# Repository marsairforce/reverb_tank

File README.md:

# A stand alone spring reverb tank

Here I wanted to investigate using op-amps to drive the tank, rather than to build a tube circuit.

I already built a tube circuit into my Traynor amp, and I am very happy with how good it sounds.

I just had this spare reverb tank sitting on my shelf with nothing to make use of it. If i can build it into a "pedal" type of effect, I can power it from standard guitar pedal power supply and use it in my audio hobby work. Like as an effect for microphone for vocals. Or drums in reaper. Any time reverb is needed so I don't need to use an effect or impulse response, Since these always sound terrible to me.

But then I had the idea, Why not just build both as a stand-alone unit. Have a switch to change between which driver is used.

## Packaging

The reverb tank is quite long. If I could build a 1U rack case for this that might be fun. But then might as well build a power supply so this plugs in. I can create a stripped down version of the op-amp power supply, having a single fixed +/-15V regulated output. That power supply is super awesome. Smooth DC ouput

The challenge is I need to be able to create a metal chassis. or shell out to buy one.

I found one from Bud Industries for about half what the Hammond mfg one was. But the Hammond one is painted. This 1U chasis needs painting then. It is about $100 to get the chassis and lid.

But the idea is I think I can fit this into a 1U chassis.

## Op-Amp Driver

I am really inspired by the design from [Elliot Sound](https://sound-au.com/project34.htm) site.

I find it curious, that when doing a google search I found several foreign websites that look like a pintrest kind of site but caching super old versions of this page, the wording is mostly the same, but the schematic showed a simple LM386 in place there for the driver to the reverb tank.

This makes me question, why?  Because before doing research into this I was thinking about using a 386 audio amplifier IC here. My theory is that it was not able to produce a good quality drive to the reverb tank. Or that the output was somewhat noisy.  Or was it just some amp design used the 386 and threatened to sue him for copyright?

Spend an evening capturing the schematic. And the power supply (see below)

## Tube Driver

I find myself again back on [The Valve Wizard](http://www.valvewizard.co.uk/reverbdriver.html) site. The discussion there is about how the using the EL84 as a driving tube is overkill and waste. Sure. But it does work.And I simply love the sound of it.

So I think I will basically take the same schematic I ended up using in the Traynor amplifier and making it a stand-alone driver into this chassis.

This is loosely based on the [Tube Town Reverb Kit](https://www.tube-town.net/cms/userfiles/media/low-reverb/kit-tubereverb.pdf)

I guess this project I am basically building that thing.

## Power Supply

The first challenge for either approach is I yet again need to build another power supply. Sometimes it feels like all I do is build a power supply for a project and by the time I figure that out I either get bored with the project and have moved on or run out of budget and give up.

If I do tubes, I need the 350V DC and the 6.3V filament supply.

If I do op-amps I need +/-15V. probably the current from the op-amp power supply project. So I can just reuse the same transformer, capacitors and a different regulator. I have a feeling this is going to be more practical. In that it is going to cost less to build, will operate with less need for cooling (e.g. in an audio rack) and have a better chance of fitting into a 1U rack chassis.

So I think I'll just build the op-amp based driver.

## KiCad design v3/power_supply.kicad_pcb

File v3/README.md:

# A second attempt at using op-amps to drive a spring reverb tank

Following the failure of the first attempt and several months, I came back to attempting this again.

This time using some of the knowledge I have learned along the way.

* To use a pre-built power supply module. These Recom power converters are basically cheaper than anything I can build, more efficient, better quality power output, And a single package can not be more convenient.

* To use the simple op-amp that powers a push pull output transistor like I had before for my desktop audio amp and speakers. I mean, here I am driving a spring. it doesn't need to be really good quality hifi audio. It just needs to make the spring move enought that we can pick up its sound.

* To use the boost converter I designed for my guitars. Here this is a v2 design I did a while ago but never got around to actually building, because I didn't need it.

So I set out the Father's day weekend to build 3 small modules.

They fit into the chassis I had used before. So that is good to recycle it.

This time, testing each component as I go on its own.

First I connected the tank on its own. Using my desk audio amplifier to drive it and just sending it back to my mic preamp to hear how it sounds.  The tank on its own is pretty quiet. Good.

I now have a regular speaker, because i built a speaker box. So connecting the reverb tank driver into a speaker to hear how it works. So the driver now works and is not buzzing. Good.  

And the same for the recovery circuit, to connect it to an audio interface and hear what the output of the tank sounds like. And it is not buzzing. Good.

I was even able to mount the spring element back into the chassis, as I originally wanted to do.

## BOM

It works out to around $250

| Part | Link |Cost |
|:--|:--|:--|
| Spring tank | 9AB2C1B | $54 |
| M2.5 standoffs, nuts, washers || $10 |
| 8" 1U rackmount chassis | [Bud Industries](https://www.digikey.ca/product-detail/en/bud-industries/CH-14401/377-1206-ND/428956) | $73 |
| Cover for chassis | [Bud Industries ](https://www.digikey.ca/product-detail/en/bud-industries/C-14431/377-1418-ND/439143) | $31 |
| Potentiometers | [Bourns](https://www.digikey.ca/product-detail/en/bourns-inc/PDA241-SRT02-103A2/PDA241-SRT02-103A2-ND/3781556) | $10 |
| Knobs | [Knurled](https://www.digikey.ca/product-detail/en/kilo-international/OEDL-75-2-5/226-1102-ND/710712) | $22 |
| Jacks | [Mono 6.35mm](https://www.digikey.ca/product-detail/en/switchcraft-inc/L112AX/SC2816-ND/1288931) | $12 |
| Switch | [Toggle](https://www.digikey.ca/product-detail/en/nkk-switches/M2011ES1W01/360-3239-ND/1049310) | $6 |
| Screw terminals | [wire to board](https://www.digikey.ca/product-detail/en/on-shore-technology-inc/OSTVN02A150/ED10561-ND/1588862) | $8 |
| Power Supply | [Recom](https://www.digikey.ca/product-detail/en/recom-power/RAC20-15DK-277/945-RAC20-15DK-277-ND/13890589) | $20 |
| Power connector | [IEC](https://www.digikey.ca/product-detail/en/qualtek/703W-00-02/Q210-ND/245551) | $2 |

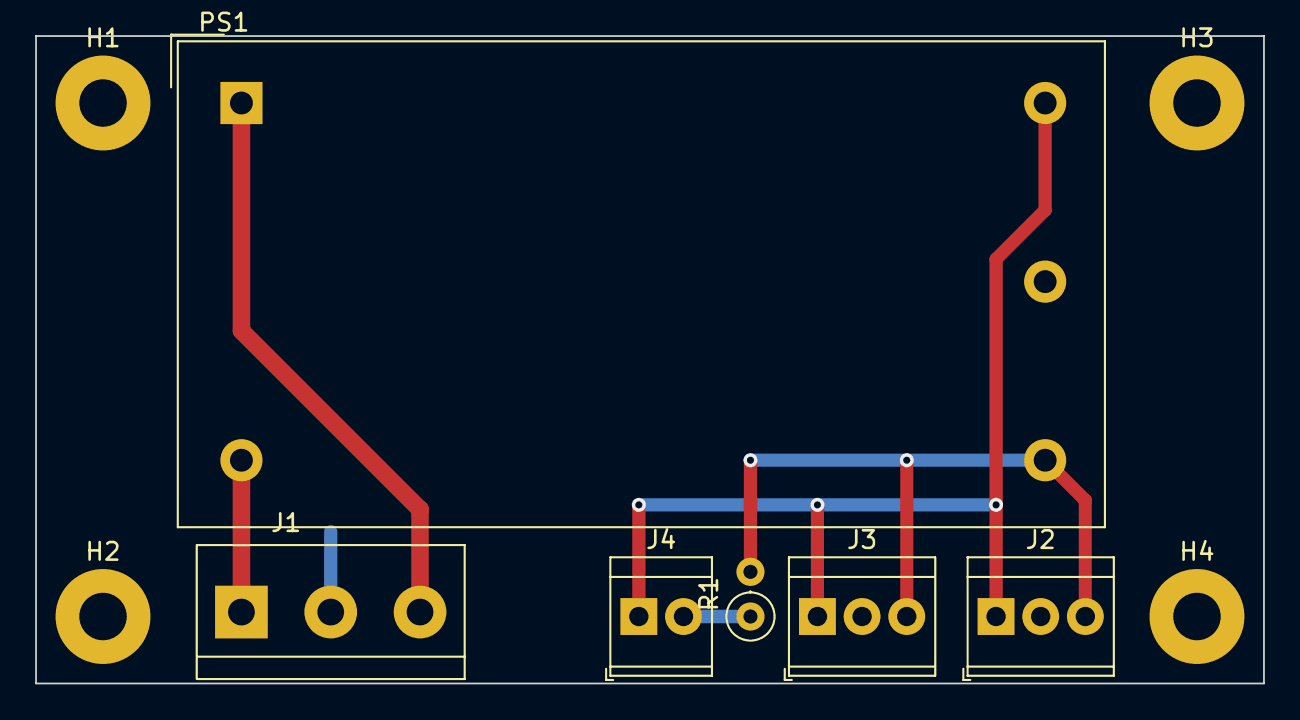
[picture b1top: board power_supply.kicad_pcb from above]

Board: 2 copper layers, 69.8 x 36.8 mm, 10 parts (0 on the bottom side), 6 nets.

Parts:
H1, H2, H3, H4: M3; MountingHole_2.7mm_Pad
J1: AC In; TerminalBlock-3_P5.08mm
J2: Power 1; TerminalBlock_1x03_P2.54mm_Horizontal
J3: Power 2; TerminalBlock_1x03_P2.54mm_Horizontal
J4: LED; TerminalBlock_1x02_P2.54mm_Horizontal
PS1: RAC20-15DK; Converter_ACDC_Recom_RAC20-xxDK_THT
R1: 4.7K; R_Axial_DIN0207_L6.3mm_D2.5mm_P2.54mm_Vertical

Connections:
/L: J1.1, PS1.2
/N: J1.3, PS1.1
GND: H1.1, H2.1, H3.1, H4.1, J1.2, J2.2, J3.2, PS1.4
unnamed: J2.1, J3.1, J4.1, PS1.5
unnamed: J2.3, J3.3, PS1.3, R1.2
unnamed: J4.2, R1.1

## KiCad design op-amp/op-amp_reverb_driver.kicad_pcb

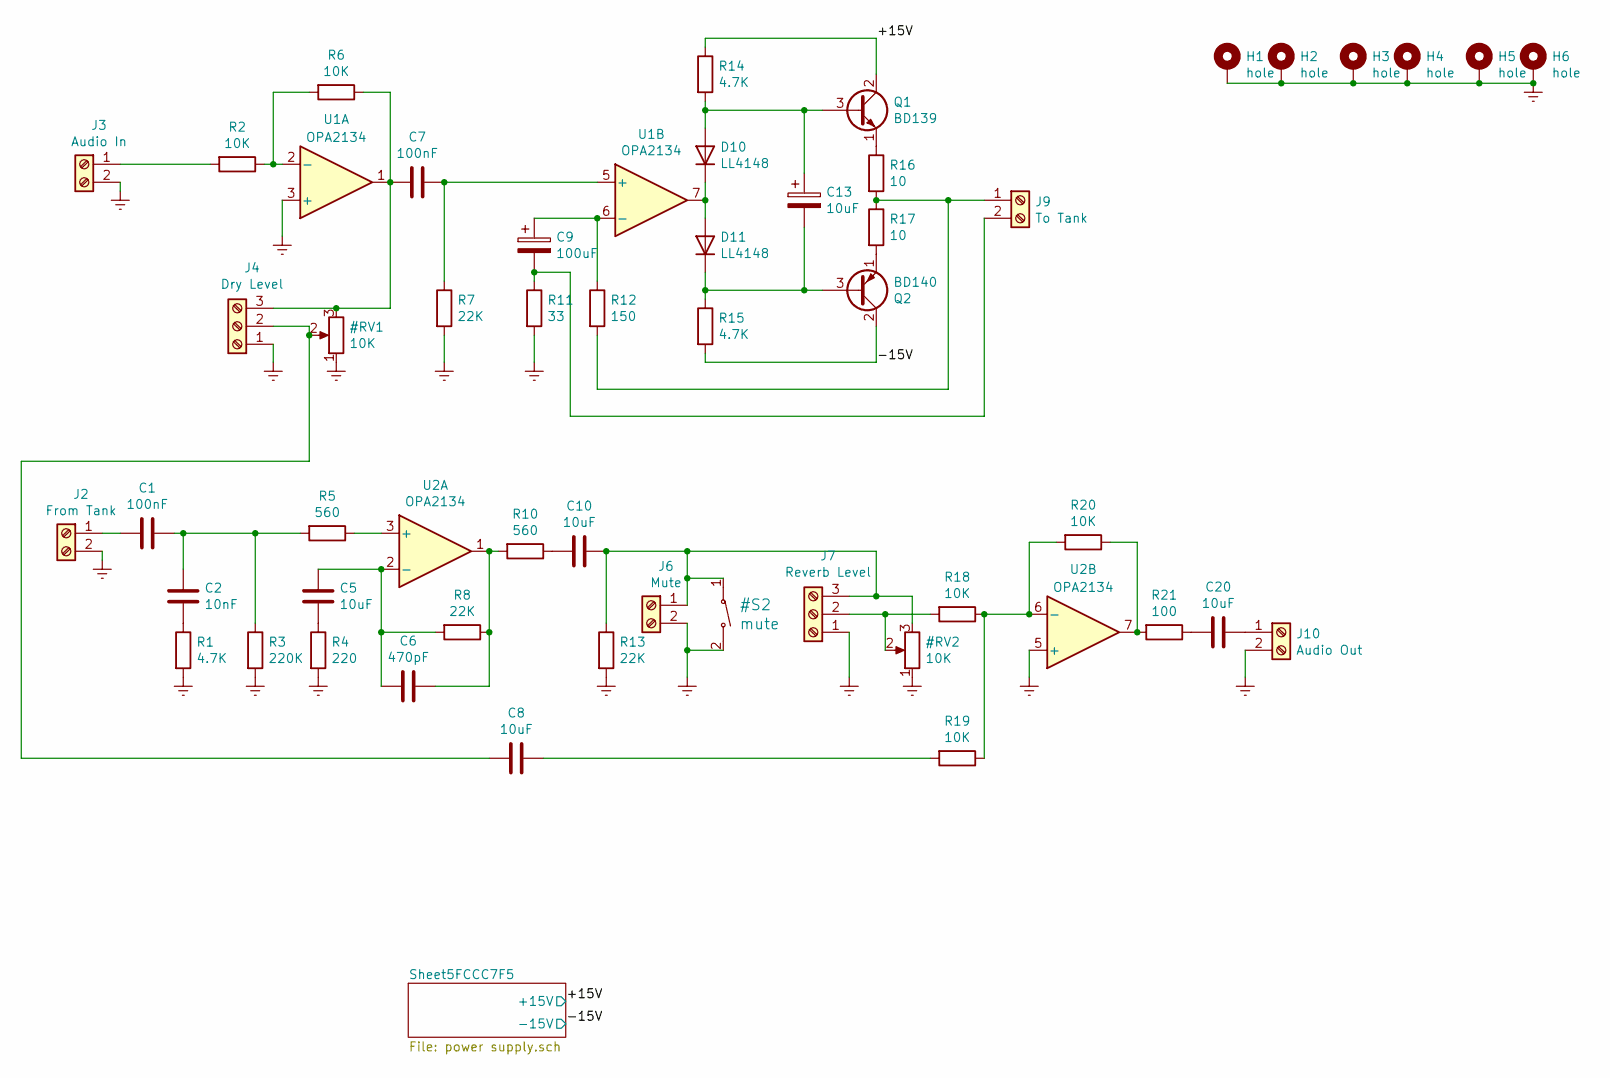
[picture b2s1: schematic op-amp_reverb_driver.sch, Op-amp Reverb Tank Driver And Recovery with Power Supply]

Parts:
C1, C7: 100nF; C_0603_1608Metric; Voltage 35V
C2: 10nF; C_0603_1608Metric
C5, C8, C10, C20: 10uF; C_0805_2012Metric
C6: 470pF; C_0603_1608Metric
C9: 100uF; CP_Elec_8x10.5; Voltage 50V
C13: 10uF; CP_Elec_4x5.8; Voltage 50V
D10, D11: LL4148; D_MiniMELF
H1, H2, H3, H4, H5, H6: hole; Mounting_Hole_Plated_M2.5
J2: From Tank; TerminalBlock_1x02_P2.54mm_Horizontal
J3: Audio In; TerminalBlock_1x02_P2.54mm_Horizontal
J4: Dry Level; TerminalBlock_1x03_P2.54mm_Horizontal
J6: Mute; TerminalBlock_1x02_P2.54mm_Horizontal
J7: Reverb Level; TerminalBlock_1x03_P2.54mm_Horizontal
J9: To Tank; TerminalBlock_1x02_P2.54mm_Horizontal
J10: Audio Out; TerminalBlock_1x02_P2.54mm_Horizontal
Q1: BD139; TO-126-3_Vertical
Q2: BD140; TO-126-3_Vertical
R1, R14, R15: 4.7K; R_0603_1608Metric
R2, R6, R18, R19, R20: 10K; R_0603_1608Metric
R3: 220K; R_0603_1608Metric
R4: 220; R_0603_1608Metric
R5, R10: 560; R_0603_1608Metric
R7, R8, R13: 22K; R_0603_1608Metric
R11: 33; R_1210_3225Metric
R12: 150; R_0603_1608Metric
R16, R17: 10; R_1210_3225Metric
R21: 100; R_0603_1608Metric
U1, U2: OPA2134; SOIC-8_3.9x4.9mm_P1.27mm

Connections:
/+15V: Q1.2 (C), R14.1; also elsewhere on the board
/-15V: Q2.2 (C), R15.2; also elsewhere on the board
unnamed: C1.1, C2.1, R3.1, R5.2
unnamed: C1.2, J2.1
unnamed: C2.2, R1.1
unnamed: C5.1, C6.1, R8.2, U2.2 (-)
unnamed: C5.2, R4.1
unnamed: C6.2, R8.1, R10.2, U2.1
unnamed: C7.1, R7.1, U1.5 (+)
unnamed: C8.1, R19.2
unnamed: C9.1, R12.1, U1.6 (-)
unnamed: C9.2, J9.2, R11.1
unnamed: C10.2, R10.1
unnamed: C13.1, D10.2 (A), Q1.3 (B), R14.2
unnamed: C13.2, D11.1 (K), Q2.3 (B), R15.1
unnamed: C20.1, J10.1
unnamed: C20.2, R21.1
unnamed: D10.1 (K), D11.2 (A), U1.7
unnamed: J3.1, R2.2
unnamed: J9.1, R12.2, R16.2, R17.1
unnamed: Q1.1 (E), R16.1
unnamed: Q2.1 (E), R17.2
unnamed: R2.1, R6.2, U1.2 (-)
unnamed: R5.1, U2.3 (+)
unnamed: R18.1, R19.1, R20.2, U2.6 (-)
unnamed: R20.1, R21.2, U2.7

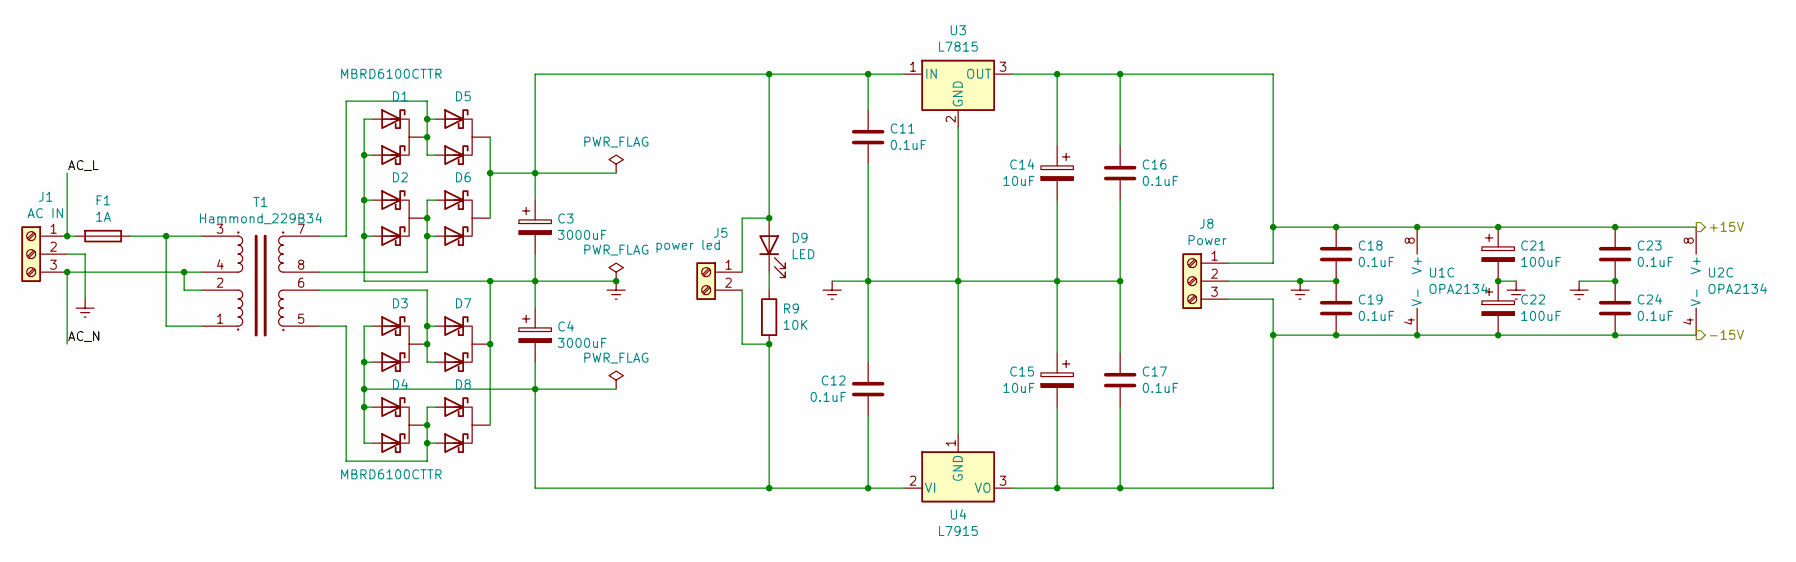
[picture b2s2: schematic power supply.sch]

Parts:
C3, C4: 3000uF; CP_Elec_18x22; Voltage 35V; Digi-Key_PN ‎P122503CT-ND‎
C11, C12, C16, C17: 0.1uF; C_0603_1608Metric; Voltage 25V; Digi-Key_PN 490-14359-2-ND
C14, C15: 10uF; C_0805_2012Metric; Voltage 50V; Digi-Key_PN ‎PCE5154CT-ND‎
C18, C19, C23, C24: 0.1uF; C_0603_1608Metric; Voltage 35V
C21, C22: 100uF; CP_Elec_8x10.5; Voltage 50V
D1, D2, D3, D4, D5, D6, D7, D8: MBRD6100CTTR; TO-252-2; Digi-Key_PN 1655-1487-1-ND
D9: LED; D_0603_1608Metric; Digi-Key_PN 160-1182-1-ND
F1: 1A; Fuseholder5x20_horiz_open_lateral_Type-II; Digi-Key_PN F4714-ND
J1: AC IN; TerminalBlock-3_P5.08mm; Digi-Key_PN ED2581-ND
J5: power led; TerminalBlock_1x02_P2.54mm_Horizontal; Digi-Key_PN ED10561-ND‎
J8: Power; TerminalBlock_1x03_P2.54mm_Horizontal
R9: 10K; R_0603_1608Metric; Digi-Key_PN CRCW06031K50FKEAC
T1: Hammond_229B34; Transformer_Hammond_229B34; Digi-Key_PN 229B34
U1, U2: OPA2134; SOIC-8_3.9x4.9mm_P1.27mm
U3: L7815; TO-252-2
U4: L7915; TO-252-2

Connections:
/+15V: C14.1, C16.1, C18.1, C21.1, C23.1, J8.1, U1.8 (V+), U2.8 (V+), U3.3 (OUT); also elsewhere on the board
/-15V: C15.2, C17.2, C19.2, C22.2, C24.2, J8.3, U1.4 (V-), U2.4 (V-), U4.3 (VO); also elsewhere on the board
/Sheet5FCCC7F5/AC_L: F1.2, J1.1
/Sheet5FCCC7F5/AC_N: J1.3, T1.2, T1.4
unnamed: C3.1, C11.1, D5.2 (A), D6.2 (A), D9.2 (A), J5.1, U3.1 (IN)
unnamed: C4.2, C12.2, D3.1 (K), D3.3 (K), D4.1 (K), D4.3 (K), J5.2, R9.2, U4.2 (VI)
unnamed: D1.2 (A), D5.1 (K), D5.3 (K), T1.7
unnamed: D2.2 (A), D6.1 (K), D6.3 (K), T1.8
unnamed: D3.2 (A), D7.1 (K), D7.3 (K), T1.6
unnamed: D4.2 (A), D8.1 (K), D8.3 (K), T1.5
unnamed: D9.1 (K), R9.1
unnamed: F1.1, T1.1, T1.3

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
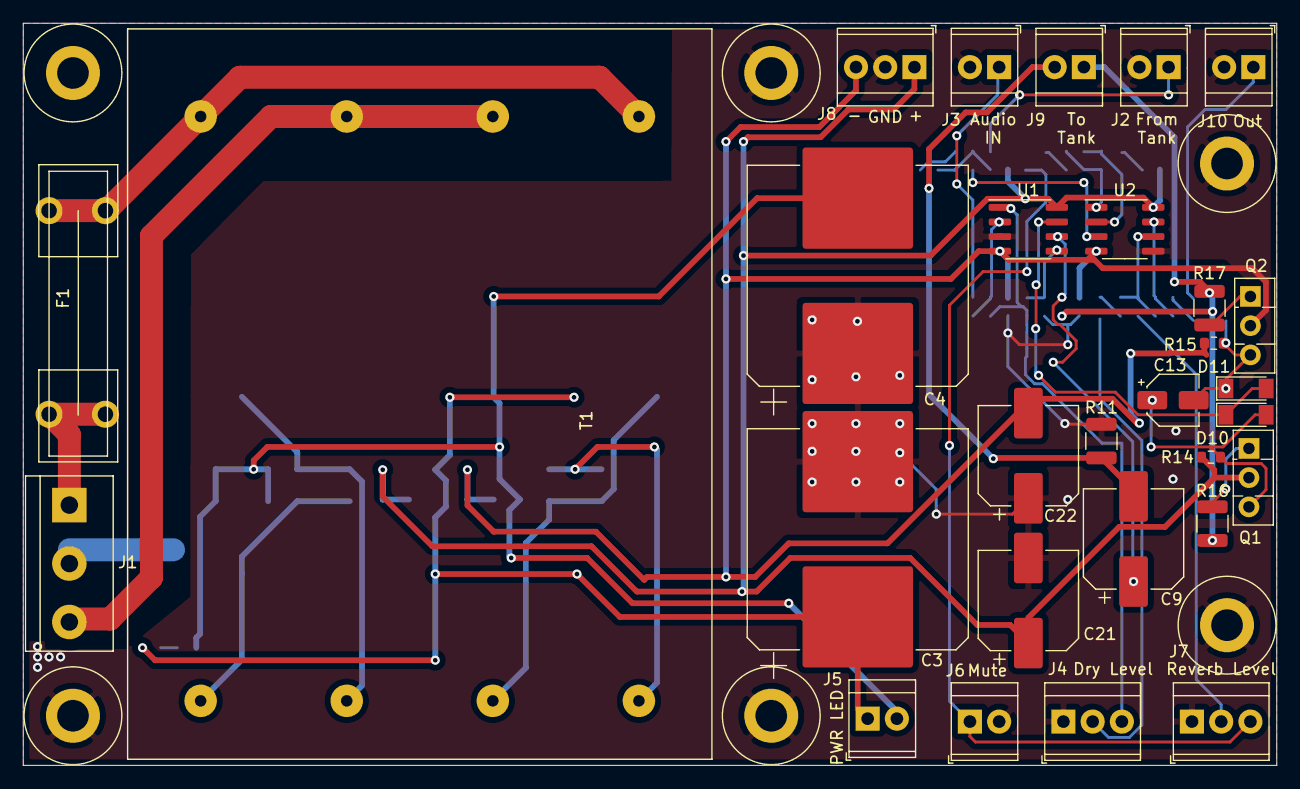
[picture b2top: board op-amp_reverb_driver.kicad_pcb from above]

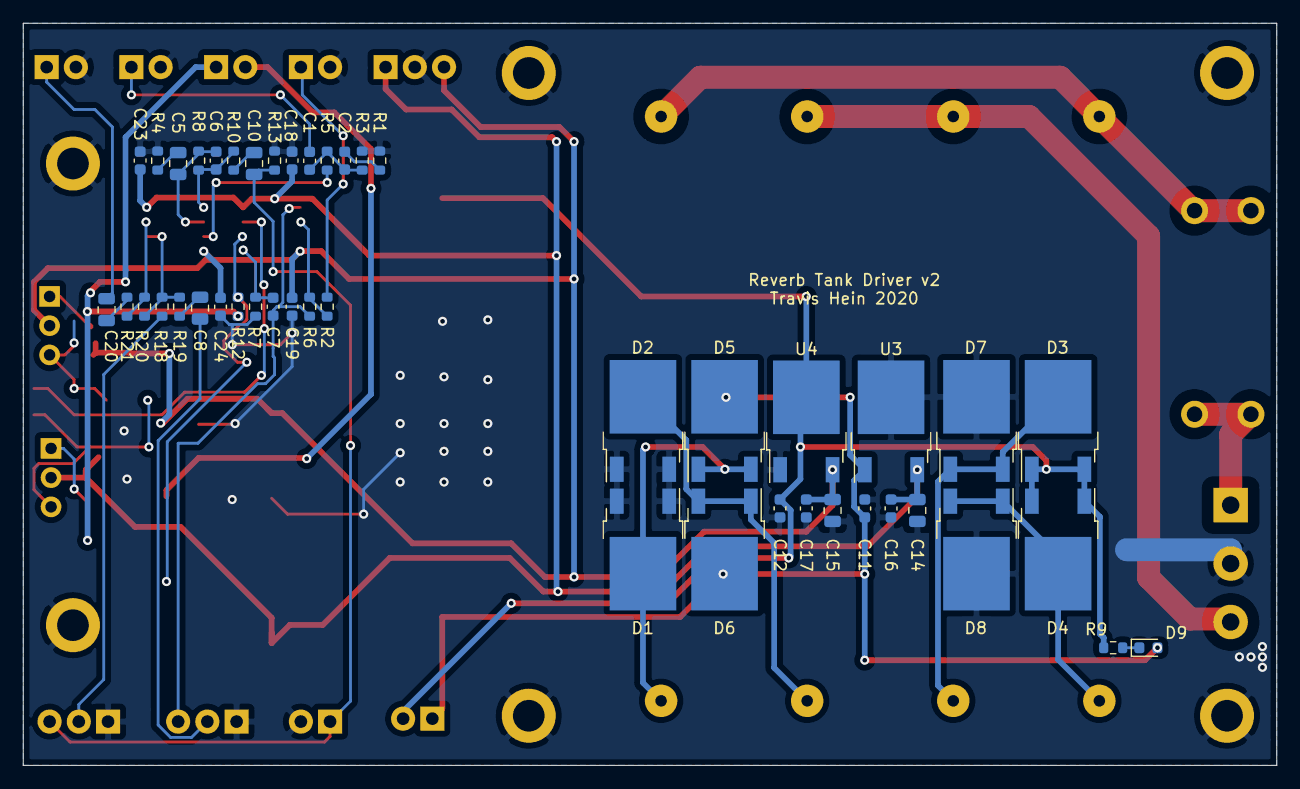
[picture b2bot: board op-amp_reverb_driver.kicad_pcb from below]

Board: 2 copper layers, 109.0 x 64.5 mm, 80 parts (45 on the bottom side), 41 nets.

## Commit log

2020-11-07 update documentation
2020-11-07 lay out the PCB and submit it to OSHPark
2020-12-12 at a natural point of fail
2021-06-21 revisit the reverb tank. create a v3. This time it works well, even with the springs inside the 1U chassis. I used experience and circuit patterns from my desktop amp, and also built the boost circui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
2021-06-29 add a test video
2021-07-03 add pcb and cad model for the power supply module
